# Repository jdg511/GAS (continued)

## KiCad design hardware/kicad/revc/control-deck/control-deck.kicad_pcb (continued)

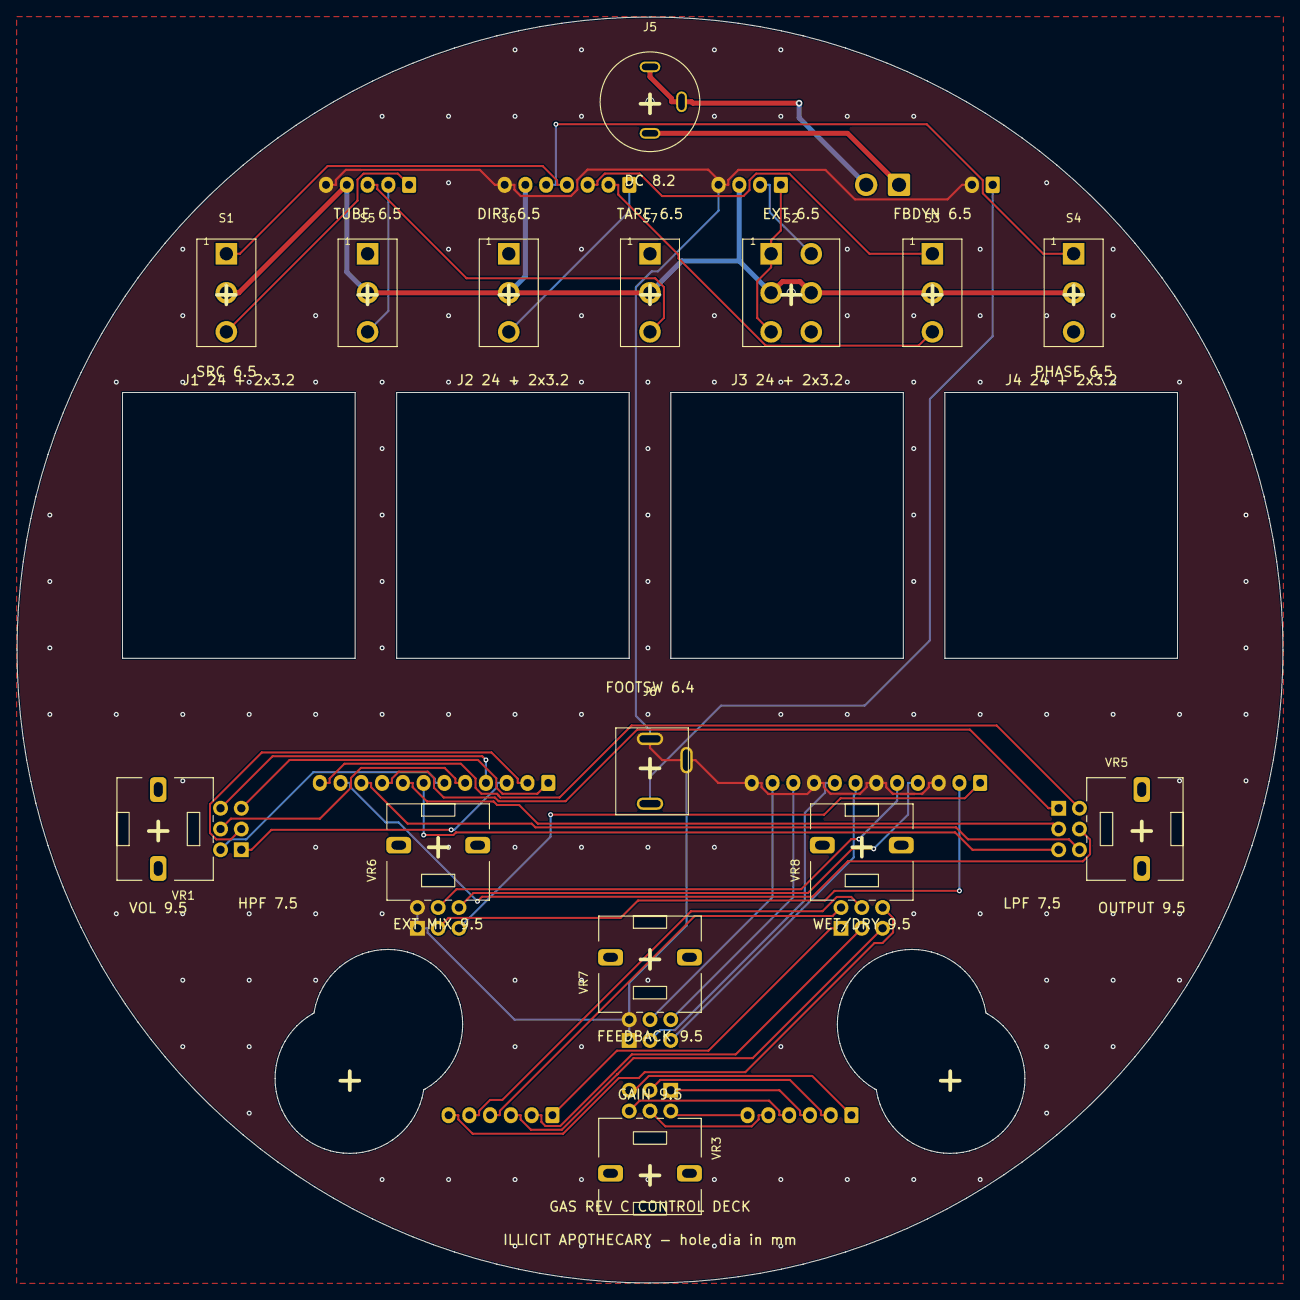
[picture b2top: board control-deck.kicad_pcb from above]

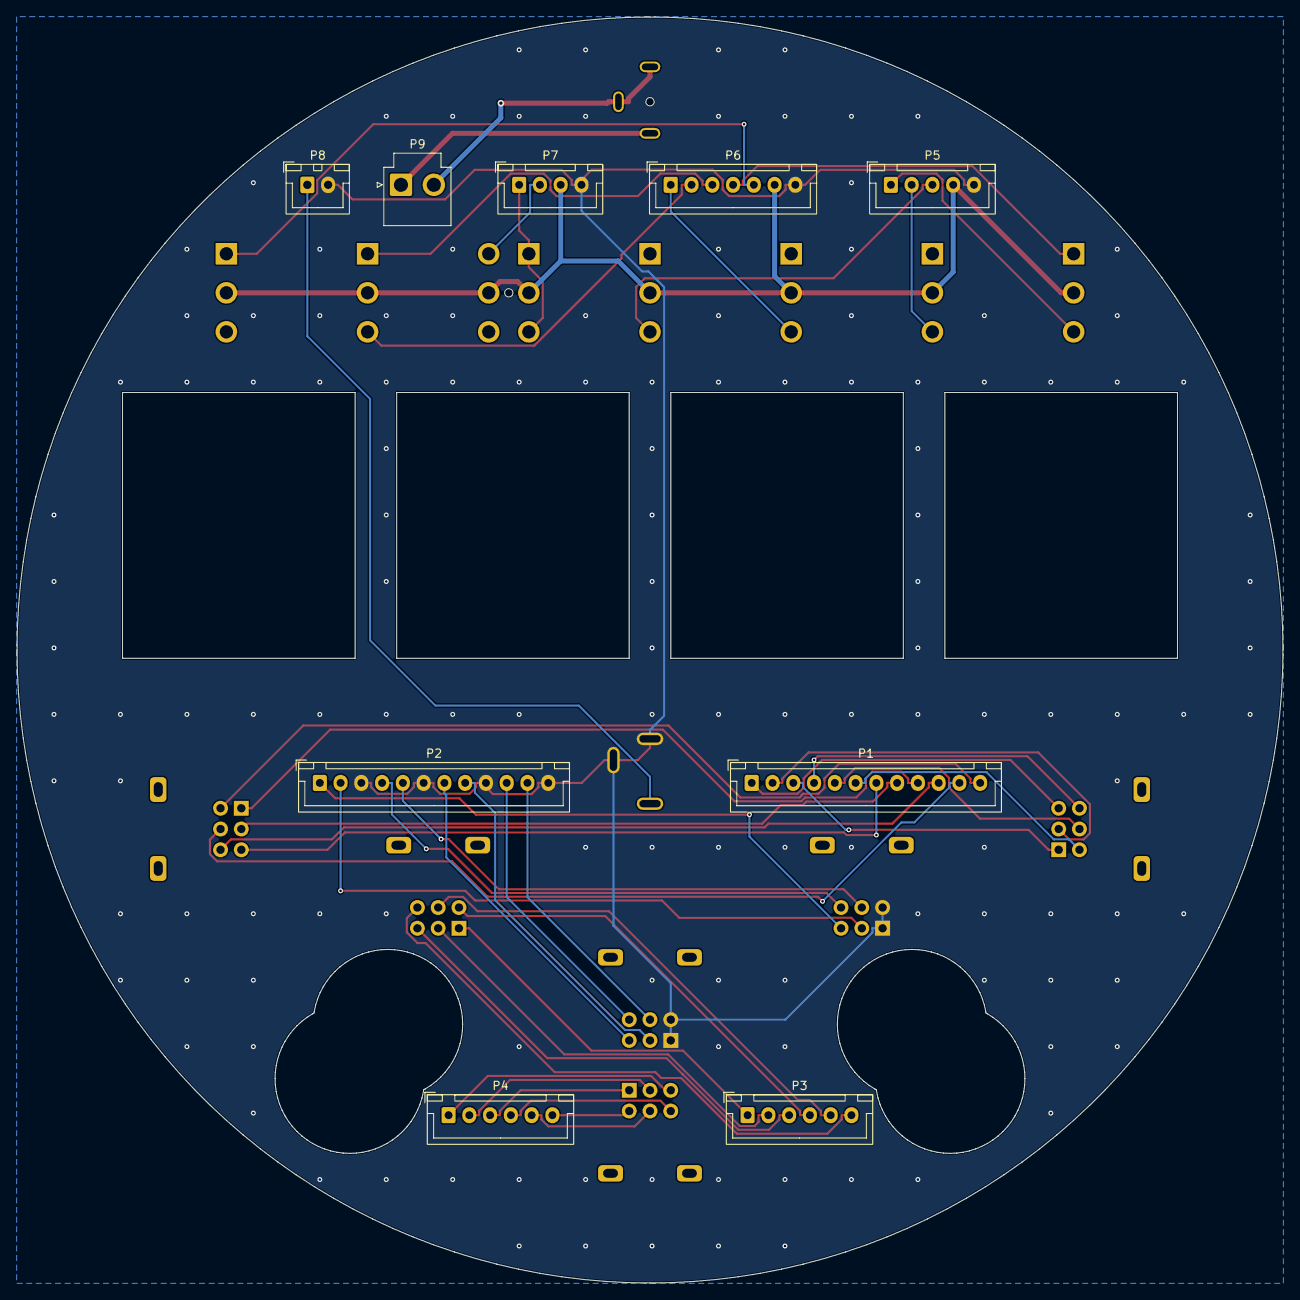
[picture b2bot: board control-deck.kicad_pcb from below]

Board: 2 copper layers, 152.4 x 152.4 mm, 24 parts (9 on the bottom side), 47 nets.

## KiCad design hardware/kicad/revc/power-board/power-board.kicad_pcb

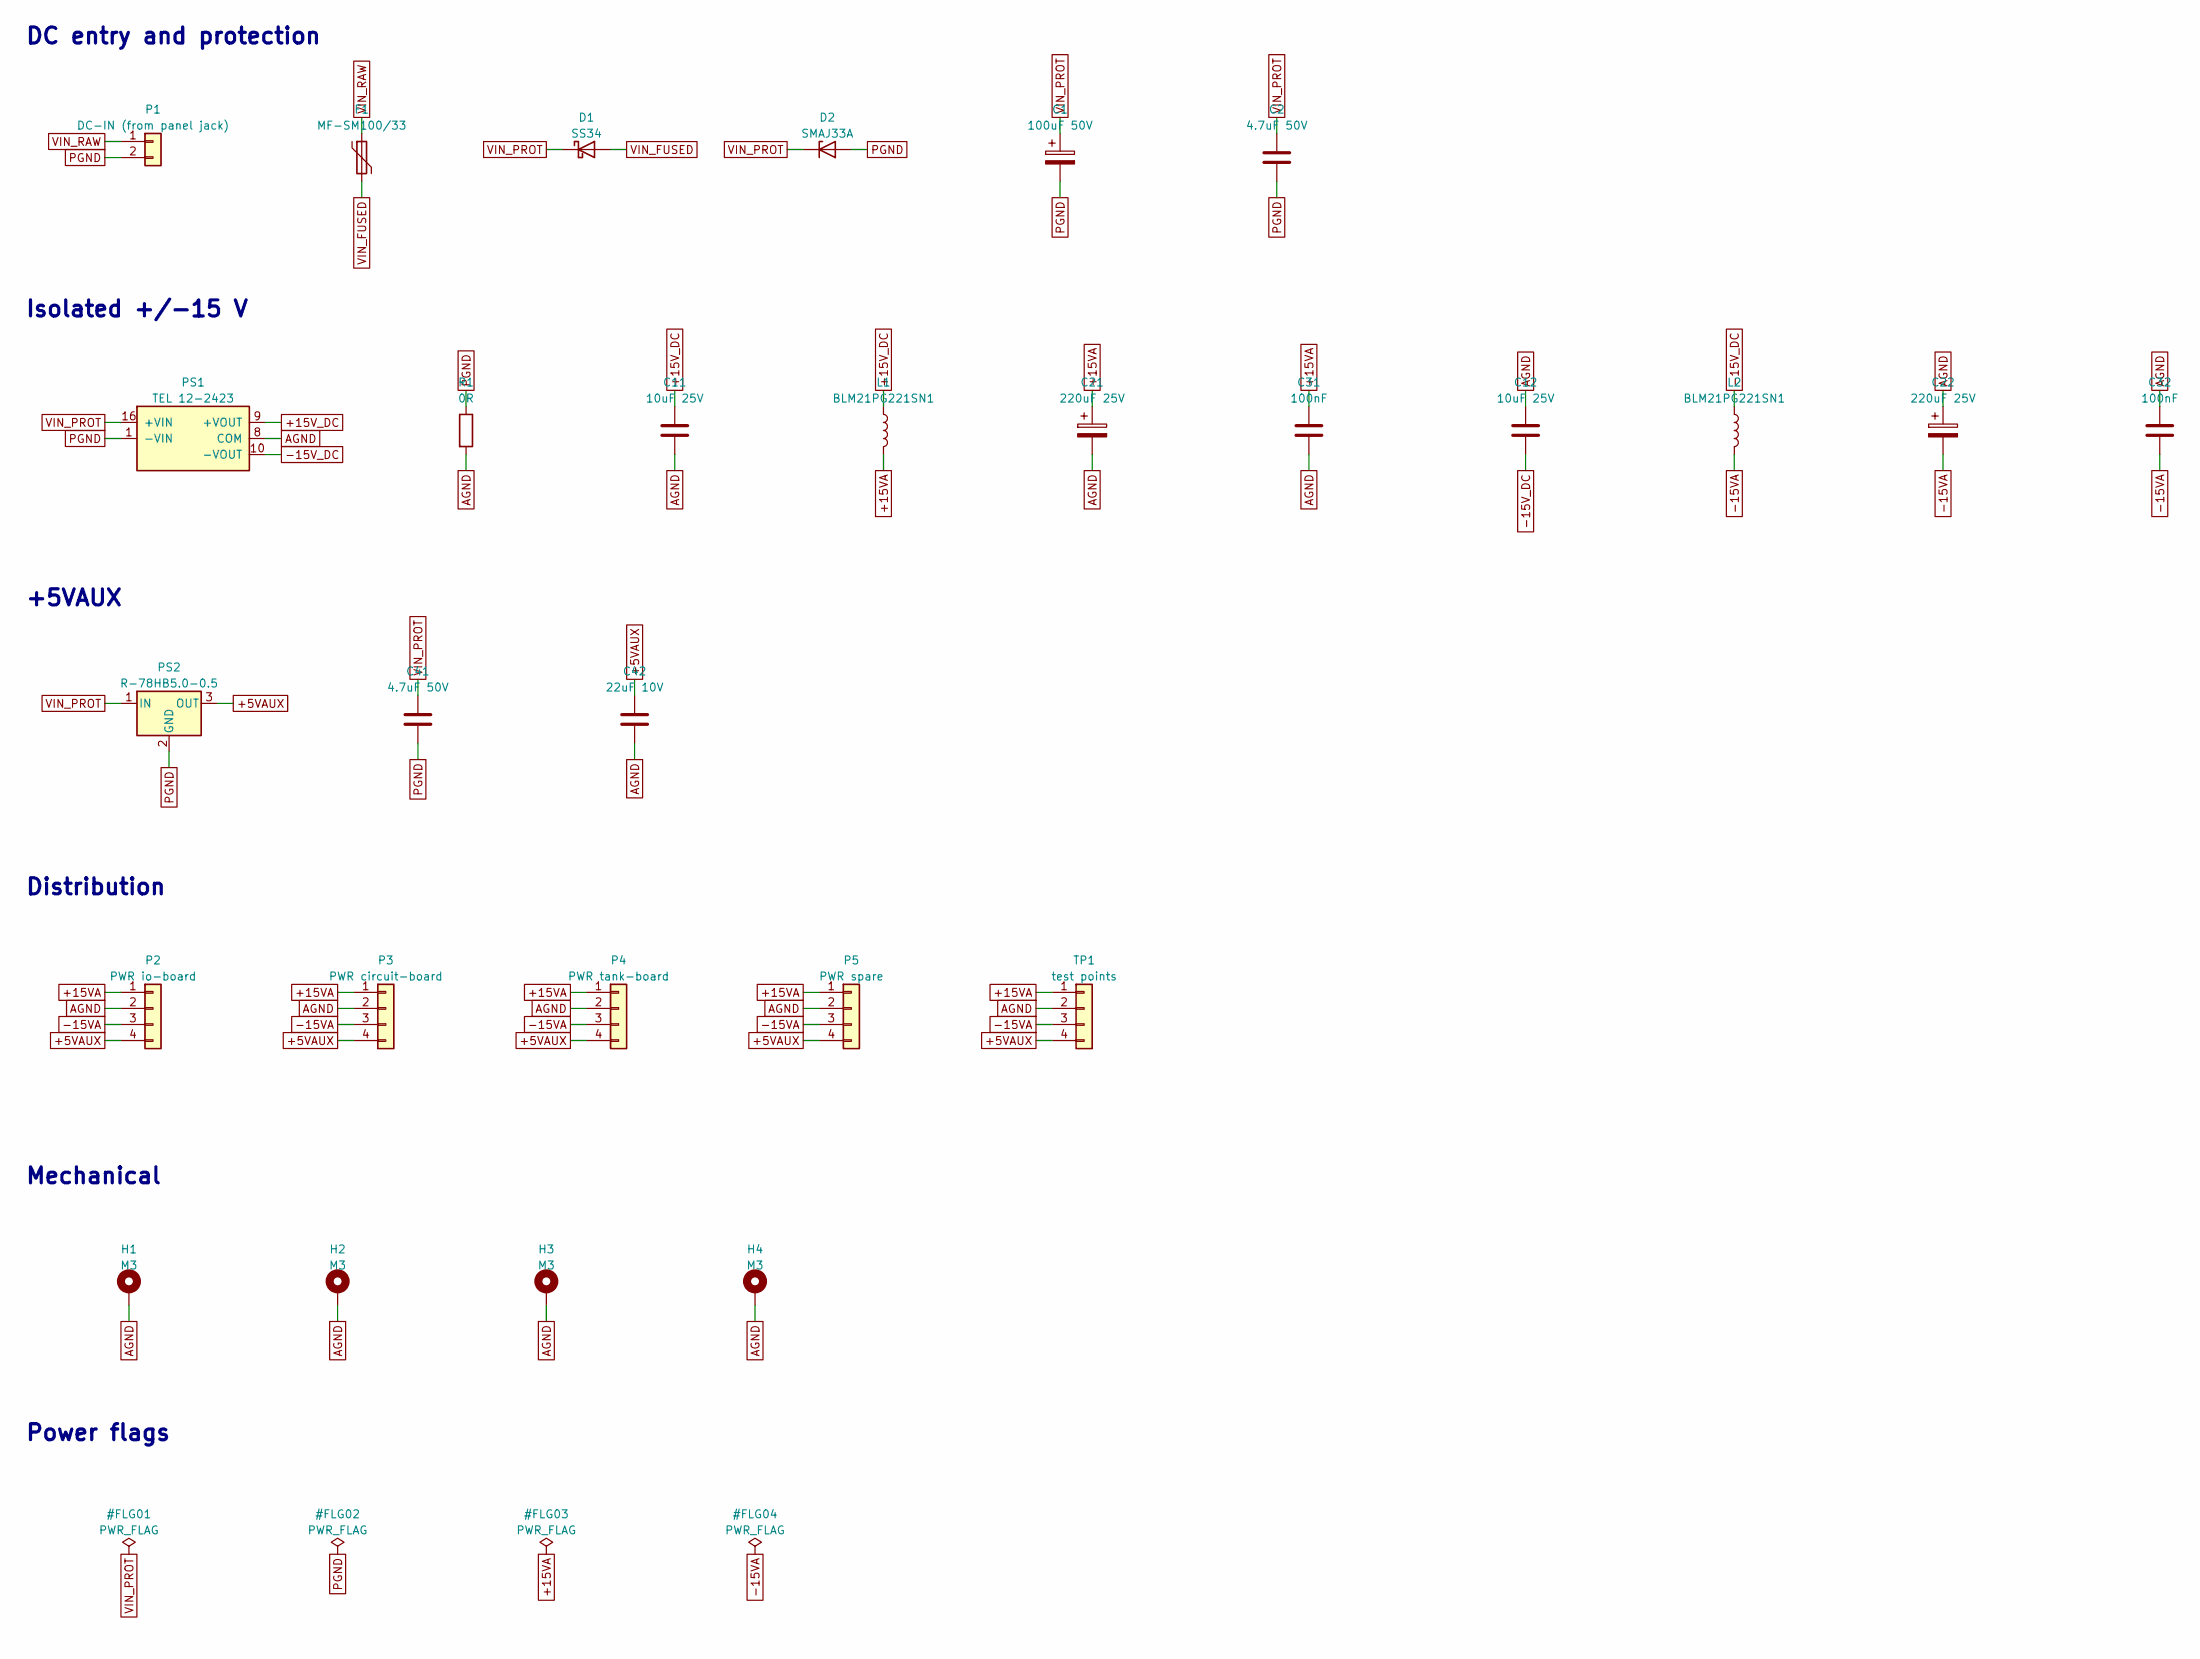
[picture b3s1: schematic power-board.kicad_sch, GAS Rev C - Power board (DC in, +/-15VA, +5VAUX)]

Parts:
C1: 100uF 50V; CP_Elec_8x10.5; MPN EEE-FK1H101P
C2, C41: 4.7uF 50V; C_1210_3225Metric; MPN GRM32ER71H475KA88L
C11, C12: 10uF 25V; C_1206_3216Metric; MPN CL31B106KAHNNNE
C21, C22: 220uF 25V; CP_Elec_8x10.5; MPN EEE-FK1E221P
C31, C32: 100nF; C_0603_1608Metric; MPN CL10B104KB8NNNC
C42: 22uF 10V; C_1206_3216Metric; MPN CL31A226KAHNNNE
D1: SS34; D_SMA; MPN SS34
D2: SMAJ33A; D_SMA; MPN SMAJ33A
F1: MF-SM100/33; Fuse_1812_4532Metric; MPN MF-SM100/33-2
H1, H2, H3, H4: M3; MountingHole_3.2mm_M3_Pad_Via
L1, L2: BLM21PG221SN1; L_0805_2012Metric; MPN BLM21PG221SN1D
P1: DC-IN (from panel jack); JST_VH_B2P-VH_1x02_P3.96mm_Vertical; MPN B2P-VH(LF)(SN)
P2: PWR io-board; JST_VH_B4P-VH_1x04_P3.96mm_Vertical; MPN B4P-VH(LF)(SN)
P3: PWR circuit-board; JST_VH_B4P-VH_1x04_P3.96mm_Vertical; MPN B4P-VH(LF)(SN)
P4: PWR tank-board; JST_VH_B4P-VH_1x04_P3.96mm_Vertical; MPN B4P-VH(LF)(SN)
P5: PWR spare; JST_VH_B4P-VH_1x04_P3.96mm_Vertical; MPN B4P-VH(LF)(SN)
PS1: TEL 12-2423; Converter_DCDC_TRACO_TEL12-xxxx_THT; MPN TEL 12-2423
PS2: R-78HB5.0-0.5; Converter_DCDC_RECOM_R-78E-0.5_THT; MPN R-78HB5.0-0.5
R1: 0R; R_1206_3216Metric; MPN RC1206JR-070RL
TP1: test points; JST_XH_B4B-XH-A_1x04_P2.50mm_Vertical; MPN B4B-XH-A(LF)(SN)

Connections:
+5VAUX: C42.1, P2.4, P3.4, P4.4, P5.4, PS2.3 (OUT), TP1.4
+15VA: C21.1, C31.1, L1.2, P2.1, P3.1, P4.1, P5.1, TP1.1
+15V_DC: C11.1, L1.1, PS1.9 (+VOUT)
-15VA: C22.2, C32.2, L2.2, P2.3, P3.3, P4.3, P5.3, TP1.3
-15V_DC: C12.2, L2.1, PS1.10 (-VOUT)
AGND: C11.2, C12.1, C21.2, C22.1, C31.2, C32.1, C42.2, H1.1, H2.1, H3.1, H4.1, P2.2, P3.2, P4.2, P5.2, PS1.8 (COM), R1.2, TP1.2
PGND: C1.2, C2.2, C41.2, D2.2 (A), P1.2, PS1.1 (-VIN), PS2.2 (GND), R1.1
VIN_FUSED: D1.2 (A), F1.2
VIN_PROT: C1.1, C2.1, C41.1, D1.1 (K), D2.1 (K), PS1.16 (+VIN), PS2.1 (IN)
VIN_RAW: F1.1, P1.1

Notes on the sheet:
DC entry and protection
Isolated +/-15 V
+5VAUX
Distribution
Mechanical
Power flags

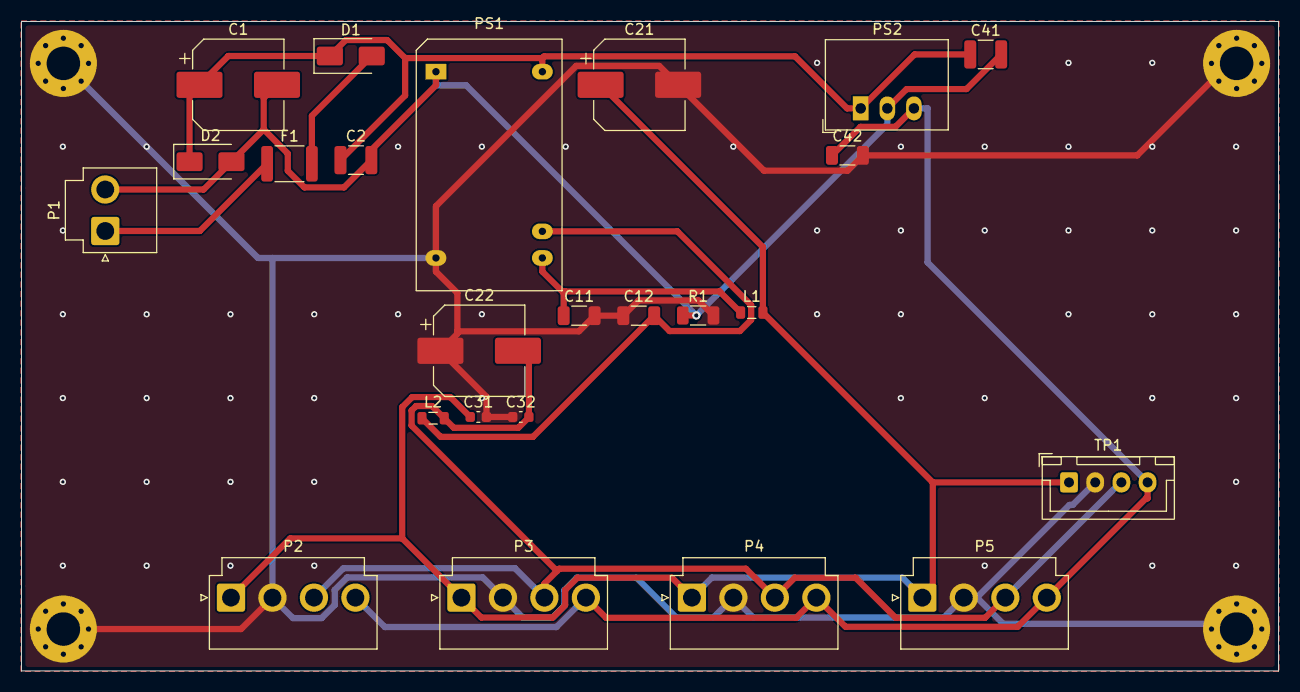
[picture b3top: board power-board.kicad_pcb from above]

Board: 2 copper layers, 120.0 x 62.0 mm, 28 parts (0 on the bottom side), 10 nets.
